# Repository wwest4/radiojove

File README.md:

# Overview

This re-implements some/all of the [radiojove receiver](https://radiojove.gsfc.nasa.gov/telescope/rcvr_manual.pdf).

For on-board components I try as much as possible to source via Digi-Key's regularly stocked items. When other vendors are used, it's indicated.

# Stages

## RF Input Bandpass
This is a 20.1 MHz bandpass filter that is applied to the input signal prior to amplification. It's based on a LC/tank filter, tunable with a variable capacitor.

### Input:
antenna in from 50-ohm coax

### Output:
filtered unamplified signal

### Parts:
| ID            | Description   | Vendor        | Part Number  |
|:------------- |:--------------|:--------------|:-------------|
| C1 | 39pF ceramic cap | Digi-Key | 399-4238-ND
| C2 | 3-40 pF trimmer cap | Digi-Key | SG3008-ND |
| C3 | 56 pF ceramic cap | Digi-Key | 399-14047-ND |
| C4 | 22 pF ceramic cap | Digi-Key | BC5148-ND |
| C5 | 10000 pF ceramic cap | Digi-Key | BC5213CT-ND |
| J2 | (wire leads for a bulkhead coax jack) | n/a | n/a |
| L1 | 470 nH inductor | Digi-Key | 495-6935-1-ND |
| L2 | 1 uH inductor | Digi-Key | M10137-ND |
| R1 | 68 ohm resistor | Digi-Key | CF14JT68R0CT-ND |

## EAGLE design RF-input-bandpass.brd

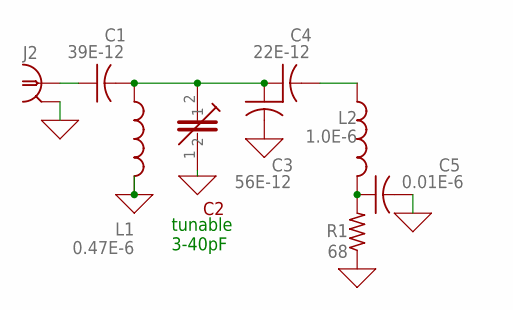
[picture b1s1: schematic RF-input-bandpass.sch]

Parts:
C1: 39E-12; C025-024X044
C2: 4.6E-12; 10_MM_TOP_BOTTOM_3_LEAD_STD
C3: 56E-12; C025-024X044
C4: 22E-12; C025-024X044
C5: 0.01E-6; C025-024X044
J2: DC 0 AC 1E-6; R141426
L1: 0.47E-6; 0204/5
L2: 1.0E-6; 0204/5
R1: 68; 0204V

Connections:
0: C2.1, C3.2, C5.2, J2.2, J2.3 (2), J2.4 (2), J2.5 (2), L1.2, R1.1
unnamed: C1.1, J2.1
unnamed: C1.2, C2.2, C3.1, C4.1, L1.1
unnamed: C4.2, L2.1
unnamed: C5.1, L2.2, R1.2

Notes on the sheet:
tunable 3-40pF

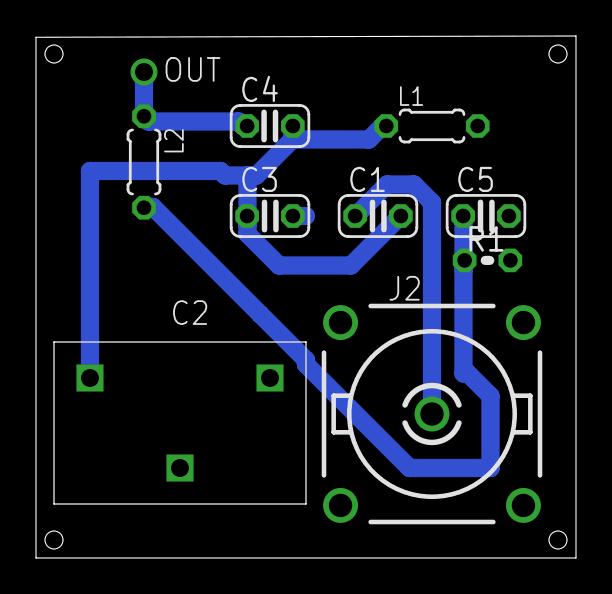
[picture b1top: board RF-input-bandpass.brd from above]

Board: 2 copper layers, 30.0 x 29.0 mm, 9 parts (0 on the bottom side), 5 nets.

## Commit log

2019-02-19 Transcribe schematic
    - add modern part changes where necessary
    - do a first-pass network QA
2019-02-19 Replace C2 and C6 package
2019-02-20 Convert schematic to kicad
2019-02-23 Convert back to eagle so we can decompose
2019-02-23 Generate RF input bandpass board
2019-02-23 Add ground plane
2019-02-23 Update trace clearance, add corner holes
2019-02-23 Increase trace and clearance size
2019-02-23 Regenerate drawing
2019-02-25 Add missing R1 to brd, invert layout png colors
2019-02-25 Add README
